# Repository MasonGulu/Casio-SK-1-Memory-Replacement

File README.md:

# Casio-SK-1-Memory-Replacement
A memory replacement PCB that adds sample loading and saving to the SK-1

This has not been tested yet and is still in early stages of development

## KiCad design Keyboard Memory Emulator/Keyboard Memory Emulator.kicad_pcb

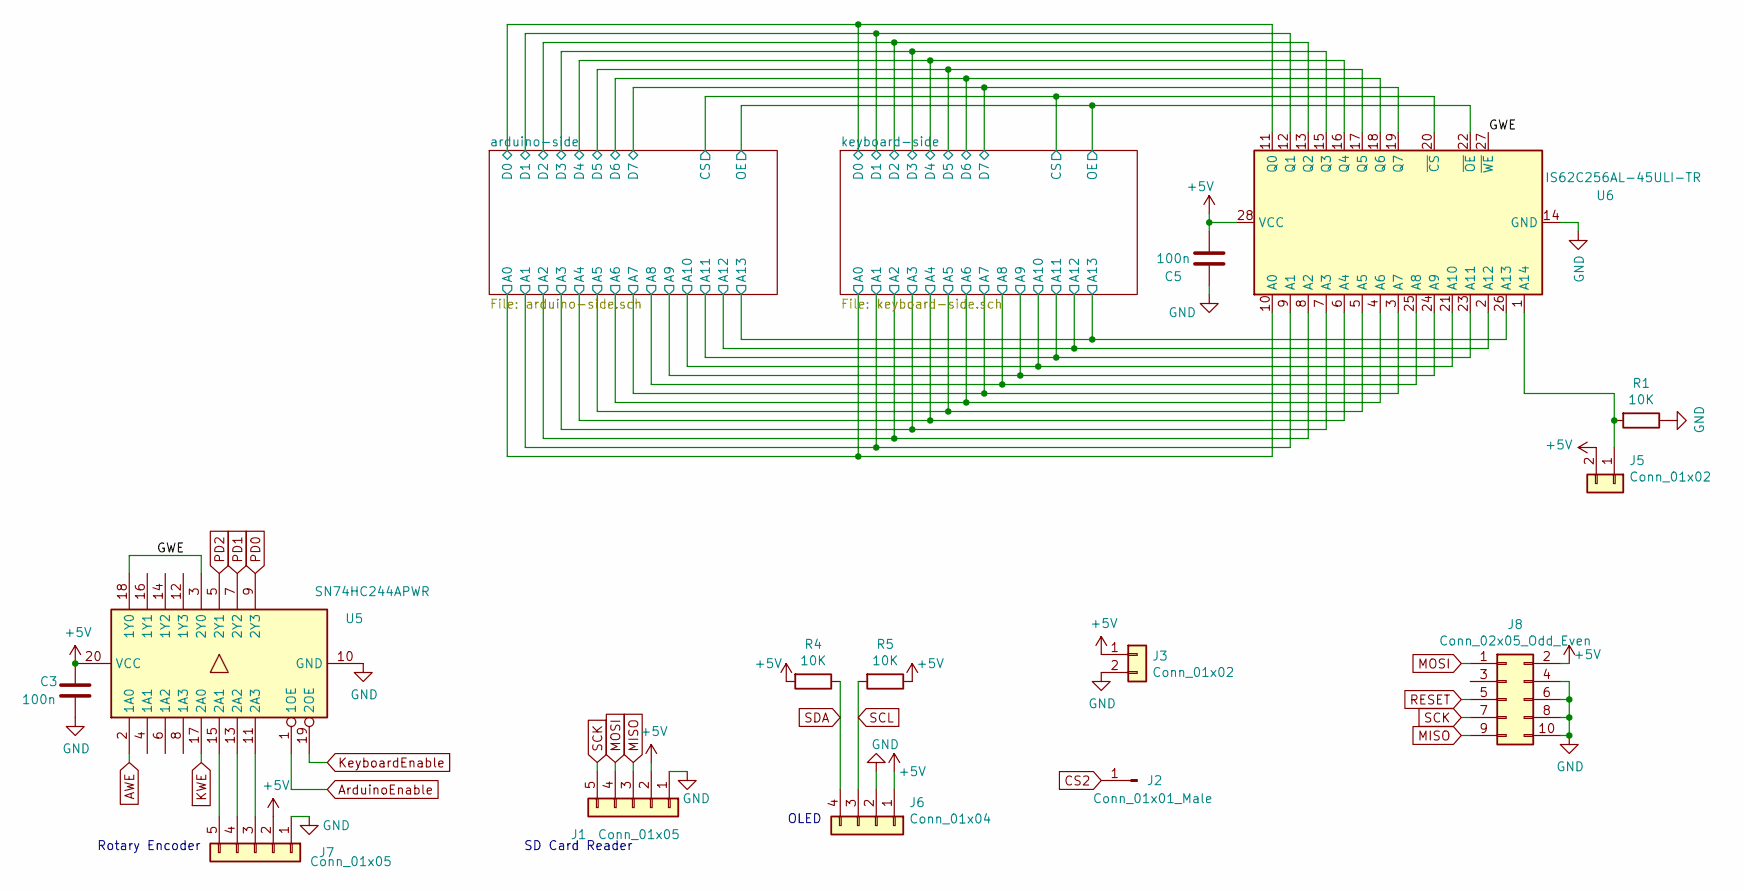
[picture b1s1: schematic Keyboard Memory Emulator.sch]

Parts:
C3, C5: 100n; C_Disc_D5.1mm_W3.2mm_P5.00mm
J1, J7: Conn_01x05; PinHeader_1x05_P2.54mm_Vertical
J2: Conn_01x01_Male; PinHeader_1x01_P2.54mm_Vertical
J3, J5: Conn_01x02; PinHeader_1x02_P2.54mm_Vertical
J6: Conn_01x04; PinHeader_1x04_P2.54mm_Vertical
J8: Conn_02x05_Odd_Even; PinHeader_2x05_P2.54mm_Vertical
R1, R4, R5: 10K; R_Axial_DIN0204_L3.6mm_D1.6mm_P5.08mm_Horizontal
U5: SN74HC244APWR; TSSOP-20_4.4x6.5mm_P0.65mm
U6: IS62C256AL-45ULI-TR; SOIC-28W_7.5x18.7mm_P1.27mm

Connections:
+5V: C3.1, C5.2, J1.2, J3.1, J5.2, J6.1, J7.2, J8.2, R4.2, R5.1, U5.20 (VCC), U6.28 (VCC); also elsewhere on the board
/GWE: U5.3 (2Y0), U5.18 (1Y0), U6.27 (~WE)
/PD0: U5.9 (2Y3)
/PD1: U5.7 (2Y2)
/PD2: U5.5 (2Y1)
/arduino-side/A0: U6.10 (A0); also elsewhere on the board
/arduino-side/A1: U6.9 (A1); also elsewhere on the board
/arduino-side/A2: U6.8 (A2); also elsewhere on the board
/arduino-side/A3: U6.7 (A3); also elsewhere on the board
/arduino-side/A4: U6.6 (A4); also elsewhere on the board
/arduino-side/A5: U6.5 (A5); also elsewhere on the board
/arduino-side/A6: U6.4 (A6); also elsewhere on the board
/arduino-side/A7: U6.3 (A7); also elsewhere on the board
/arduino-side/A8: U6.25 (A8); also elsewhere on the board
/arduino-side/A9: U6.24 (A9); also elsewhere on the board
/arduino-side/A10: U6.21 (A10); also elsewhere on the board
/arduino-side/A11: U6.23 (A11); also elsewhere on the board
/arduino-side/A12: U6.2 (A12); also elsewhere on the board
/arduino-side/A13: U6.26 (A13); also elsewhere on the board
/arduino-side/CS: U6.20 (~CS); also elsewhere on the board
/arduino-side/D0: U6.11 (Q0); also elsewhere on the board
/arduino-side/D1: U6.12 (Q1); also elsewhere on the board
/arduino-side/D2: U6.13 (Q2); also elsewhere on the board
/arduino-side/D3: U6.15 (Q3); also elsewhere on the board
/arduino-side/D4: U6.16 (Q4); also elsewhere on the board
/arduino-side/D5: U6.17 (Q5); also elsewhere on the board
/arduino-side/D6: U6.18 (Q6); also elsewhere on the board
/arduino-side/D7: U6.19 (Q7); also elsewhere on the board
AWE: U5.2 (1A0); also elsewhere on the board
ArduinoEnable: U5.1 (1OE); also elsewhere on the board
CS2: J2.1; also elsewhere on the board
GND: C3.2, C5.1, J1.1, J3.2, J6.2, J7.1, J8.4, J8.6, J8.8, J8.10, R1.1, U5.10 (GND), U6.14 (GND); also elsewhere on the board
KWE: U5.17 (2A0); also elsewhere on the board
KeyboardEnable: U5.19 (2OE); also elsewhere on the board
MISO: J1.3, J8.9; also elsewhere on the board
MOSI: J1.4, J8.1; also elsewhere on the board
unnamed: J5.1, R1.2, U6.1 (A14)
unnamed: J7.3, U5.11 (2A3)
unnamed: J7.4, U5.13 (2A2)
unnamed: J7.5, U5.15 (2A1)
OE: U6.22 (~OE); also elsewhere on the board
RESET: J8.5; also elsewhere on the board
SCK: J1.5, J8.7; also elsewhere on the board
SCL: J6.3, R5.2; also elsewhere on the board
SDA: J6.4, R4.1; also elsewhere on the board

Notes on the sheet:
SD Card Reader
OLED
Rotary Encoder

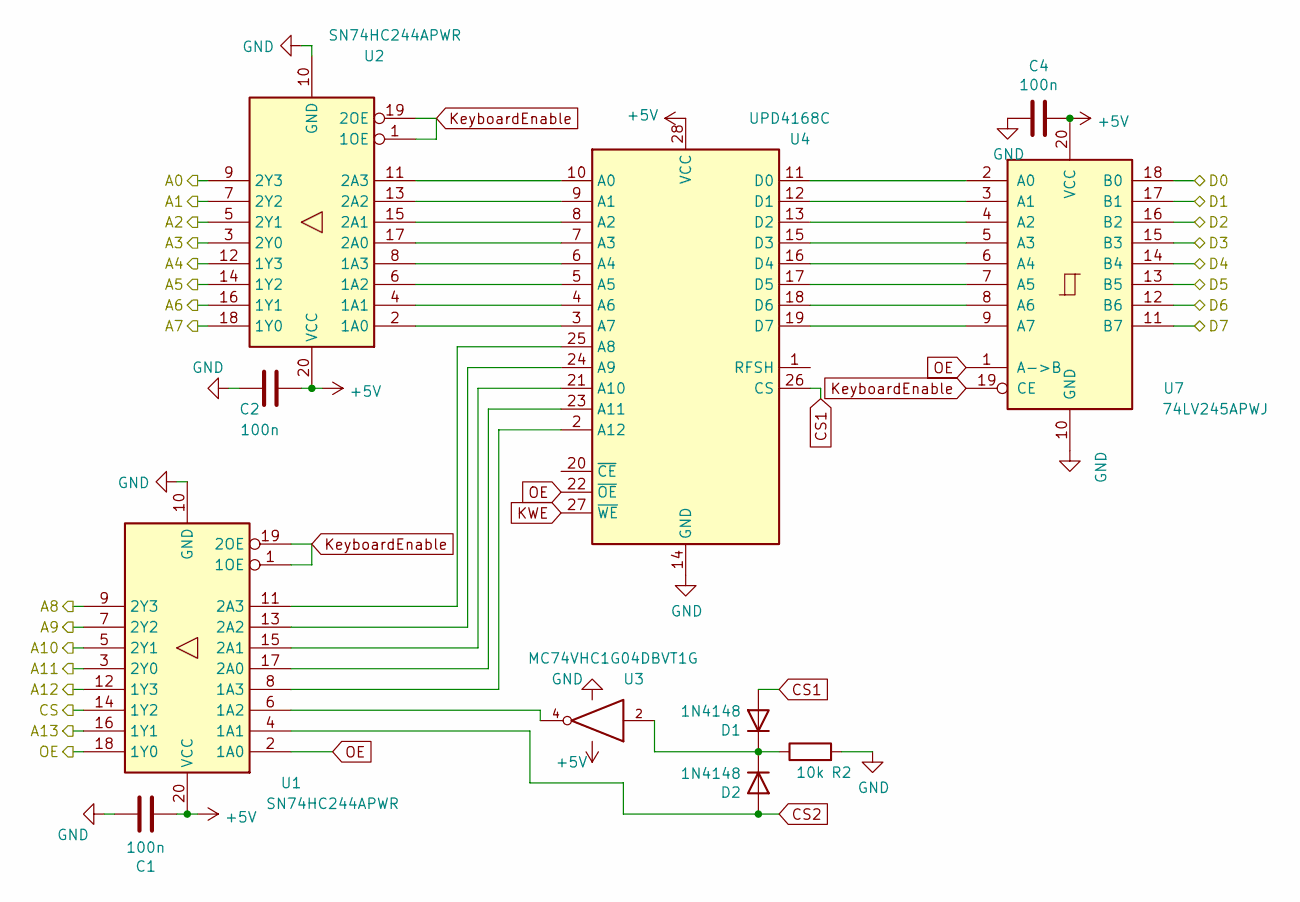
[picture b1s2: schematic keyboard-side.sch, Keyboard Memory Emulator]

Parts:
C1, C2, C4: 100n; C_Disc_D5.1mm_W3.2mm_P5.00mm
D1, D2: 1N4148; D_DO-34_SOD68_P7.62mm_Horizontal
R2: 10k; R_Axial_DIN0204_L3.6mm_D1.6mm_P5.08mm_Horizontal
U1, U2: SN74HC244APWR; TSSOP-20_4.4x6.5mm_P0.65mm
U3: MC74VHC1G04DBVT1G; SC-74A
U4: UPD4168C; DIP-28_W15.24mm
U7: 74LV245APWJ; TSSOP-20_4.4x6.5mm_P0.65mm

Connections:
+5V: C1.2, C2.1, C4.1, U1.20 (VCC), U2.20 (VCC), U3.5 (VCC), U4.28 (VCC), U7.20 (VCC); also elsewhere on the board
/arduino-side/A0: U2.9 (2Y3); also elsewhere on the board
/arduino-side/A1: U2.7 (2Y2); also elsewhere on the board
/arduino-side/A2: U2.5 (2Y1); also elsewhere on the board
/arduino-side/A3: U2.3 (2Y0); also elsewhere on the board
/arduino-side/A4: U2.12 (1Y3); also elsewhere on the board
/arduino-side/A5: U2.14 (1Y2); also elsewhere on the board
/arduino-side/A6: U2.16 (1Y1); also elsewhere on the board
/arduino-side/A7: U2.18 (1Y0); also elsewhere on the board
/arduino-side/A8: U1.9 (2Y3); also elsewhere on the board
/arduino-side/A9: U1.7 (2Y2); also elsewhere on the board
/arduino-side/A10: U1.5 (2Y1); also elsewhere on the board
/arduino-side/A11: U1.3 (2Y0); also elsewhere on the board
/arduino-side/A12: U1.12 (1Y3); also elsewhere on the board
/arduino-side/A13: U1.16 (1Y1); also elsewhere on the board
/arduino-side/CS: U1.14 (1Y2); also elsewhere on the board
/arduino-side/D0: U7.18 (B0); also elsewhere on the board
/arduino-side/D1: U7.17 (B1); also elsewhere on the board
/arduino-side/D2: U7.16 (B2); also elsewhere on the board
/arduino-side/D3: U7.15 (B3); also elsewhere on the board
/arduino-side/D4: U7.14 (B4); also elsewhere on the board
/arduino-side/D5: U7.13 (B5); also elsewhere on the board
/arduino-side/D6: U7.12 (B6); also elsewhere on the board
/arduino-side/D7: U7.11 (B7); also elsewhere on the board
CS1: D1.2 (A), U4.26 (CS)
CS2: D2.2 (A), U1.4 (1A1); also elsewhere on the board
GND: C1.1, C2.2, C4.2, R2.2, U1.10 (GND), U2.10 (GND), U3.3 (GND), U4.14 (GND), U7.10 (GND); also elsewhere on the board
KWE: U4.27 (~WE~); also elsewhere on the board
KeyboardEnable: U1.1 (1OE), U1.19 (2OE), U2.1 (1OE), U2.19 (2OE), U7.19 (CE); also elsewhere on the board
unnamed: D1.1 (K), D2.1 (K), R2.1, U3.2
unnamed: U1.6 (1A2), U3.4
unnamed: U1.8 (1A3), U4.2 (A12)
unnamed: U1.11 (2A3), U4.25 (A8)
unnamed: U1.13 (2A2), U4.24 (A9)
unnamed: U1.15 (2A1), U4.21 (A10)
unnamed: U1.17 (2A0), U4.23 (A11)
unnamed: U2.2 (1A0), U4.3 (A7)
unnamed: U2.4 (1A1), U4.4 (A6)
unnamed: U2.6 (1A2), U4.5 (A5)
unnamed: U2.8 (1A3), U4.6 (A4)
unnamed: U2.11 (2A3), U4.10 (A0)
unnamed: U2.13 (2A2), U4.9 (A1)
unnamed: U2.15 (2A1), U4.8 (A2)
unnamed: U2.17 (2A0), U4.7 (A3)
unnamed: U4.11 (D0), U7.2 (A0)
unnamed: U4.12 (D1), U7.3 (A1)
unnamed: U4.13 (D2), U7.4 (A2)
unnamed: U4.15 (D3), U7.5 (A3)
unnamed: U4.16 (D4), U7.6 (A4)
unnamed: U4.17 (D5), U7.7 (A5)
unnamed: U4.18 (D6), U7.8 (A6)
unnamed: U4.19 (D7), U7.9 (A7)
OE: U1.2 (1A0), U1.18 (1Y0), U4.22 (~OE~), U7.1 (A->B); also elsewhere on the board

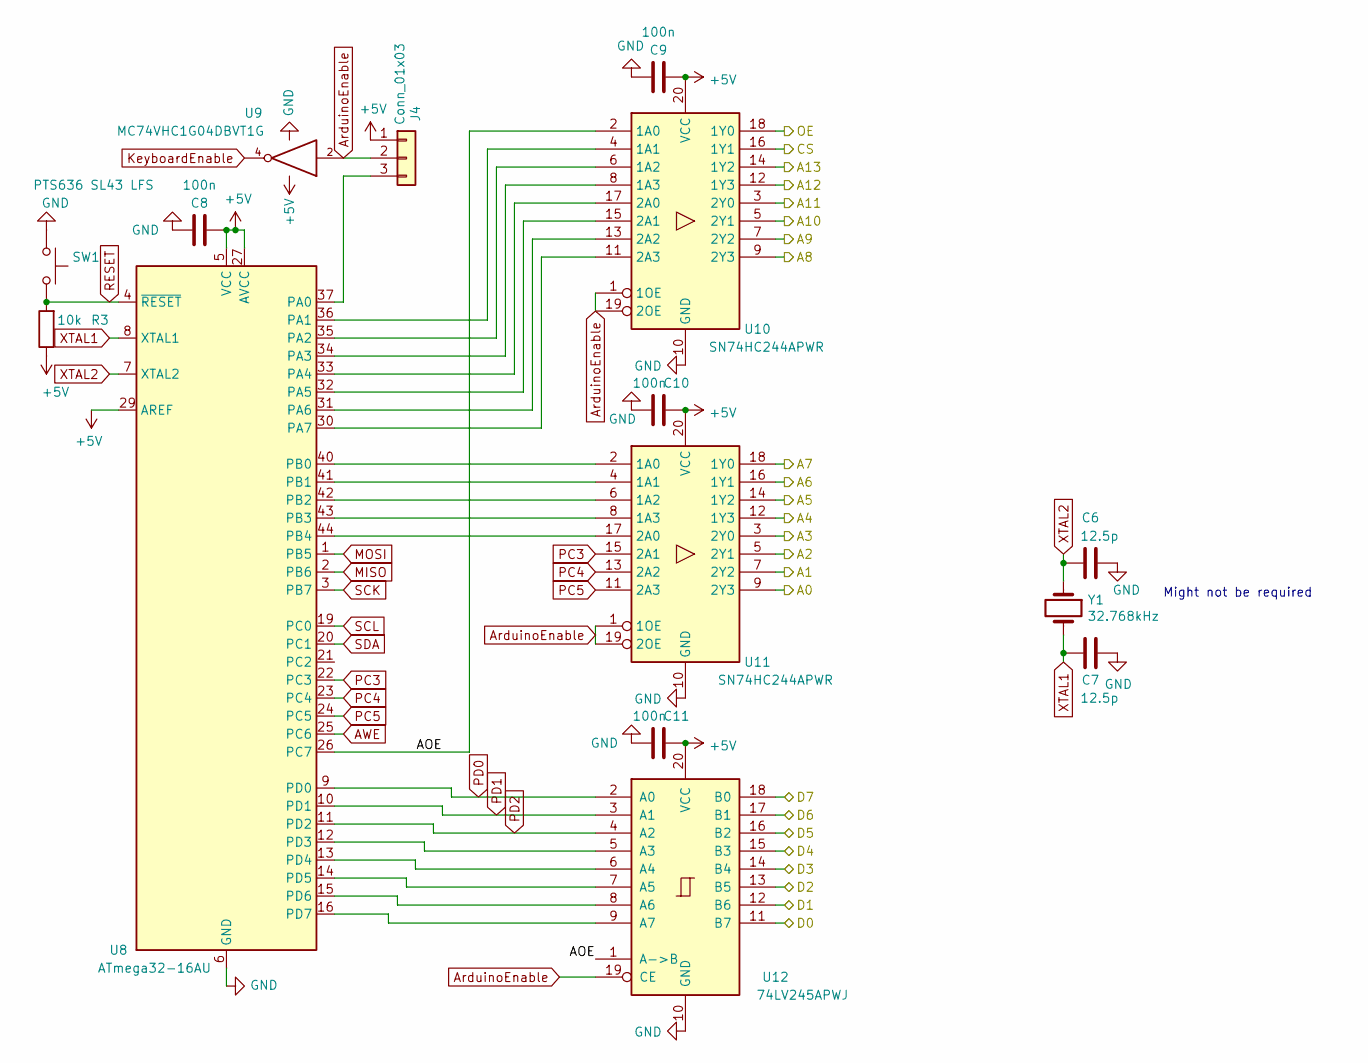
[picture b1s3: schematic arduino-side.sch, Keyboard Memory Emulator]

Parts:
C6, C7: 12.5p; C_Disc_D5.1mm_W3.2mm_P5.00mm
C8, C9, C10, C11: 100n; C_Disc_D5.1mm_W3.2mm_P5.00mm
J4: Conn_01x03; PinHeader_1x03_P2.54mm_Vertical
R3: 10k; R_Axial_DIN0204_L3.6mm_D1.6mm_P5.08mm_Horizontal
SW1: PTS636 SL43 LFS; SW_SPST_REED_CT05-XXXX-G1
U8: ATmega32-16AU; TQFP-44_10x10mm_P0.8mm
U9: MC74VHC1G04DBVT1G; SC-74A
U10, U11: SN74HC244APWR; TSSOP-20_4.4x6.5mm_P0.65mm
U12: 74LV245APWJ; TSSOP-20_4.4x6.5mm_P0.65mm
Y1: 32.768kHz; Crystal_C26-LF_D2.1mm_L6.5mm_Horizontal

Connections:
+5V: C8.2, C9.2, C10.2, C11.2, J4.1, R3.1, U8.5 (VCC), U8.17 (VCC), U8.27 (AVCC), U8.29 (AREF), U8.38 (VCC), U9.5 (VCC), U10.20 (VCC), U11.20 (VCC), U12.20 (VCC); also elsewhere on the board
/arduino-side/A0: U11.9 (2Y3); also elsewhere on the board
/arduino-side/A1: U11.7 (2Y2); also elsewhere on the board
/arduino-side/A2: U11.5 (2Y1); also elsewhere on the board
/arduino-side/A3: U11.3 (2Y0); also elsewhere on the board
/arduino-side/A4: U11.12 (1Y3); also elsewhere on the board
/arduino-side/A5: U11.14 (1Y2); also elsewhere on the board
/arduino-side/A6: U11.16 (1Y1); also elsewhere on the board
/arduino-side/A7: U11.18 (1Y0); also elsewhere on the board
/arduino-side/A8: U10.9 (2Y3); also elsewhere on the board
/arduino-side/A9: U10.7 (2Y2); also elsewhere on the board
/arduino-side/A10: U10.5 (2Y1); also elsewhere on the board
/arduino-side/A11: U10.3 (2Y0); also elsewhere on the board
/arduino-side/A12: U10.12 (1Y3); also elsewhere on the board
/arduino-side/A13: U10.14 (1Y2); also elsewhere on the board
/arduino-side/AOE: U8.26 (PC7), U10.2 (1A0), U12.1 (A->B)
/arduino-side/CS: U10.16 (1Y1); also elsewhere on the board
/arduino-side/D0: U12.11 (B7); also elsewhere on the board
/arduino-side/D1: U12.12 (B6); also elsewhere on the board
/arduino-side/D2: U12.13 (B5); also elsewhere on the board
/arduino-side/D3: U12.14 (B4); also elsewhere on the board
/arduino-side/D4: U12.15 (B3); also elsewhere on the board
/arduino-side/D5: U12.16 (B2); also elsewhere on the board
/arduino-side/D6: U12.17 (B1); also elsewhere on the board
/arduino-side/D7: U12.18 (B0); also elsewhere on the board
/arduino-side/PD0: U8.9 (PD0), U12.2 (A0)
/arduino-side/PD1: U8.10 (PD1), U12.3 (A1)
/arduino-side/PD2: U8.11 (PD2), U12.4 (A2)
AWE: U8.25 (PC6); also elsewhere on the board
ArduinoEnable: J4.2, U9.2, U10.1 (1OE), U10.19 (2OE), U11.1 (1OE), U11.19 (2OE), U12.19 (CE); also elsewhere on the board
GND: C6.1, C7.1, C8.1, C9.1, C10.1, C11.1, SW1.1, U8.6 (GND), U8.18 (GND), U8.28 (GND), U8.39 (GND), U9.3 (GND), U10.10 (GND), U11.10 (GND), U12.10 (GND); also elsewhere on the board
KeyboardEnable: U9.4; also elsewhere on the board
MISO: U8.2 (PB6); also elsewhere on the board
MOSI: U8.1 (PB5); also elsewhere on the board
unnamed: J4.3, U8.37 (PA0)
unnamed: U8.36 (PA1), U10.4 (1A1)
unnamed: U8.35 (PA2), U10.6 (1A2)
unnamed: U8.34 (PA3), U10.8 (1A3)
unnamed: U8.30 (PA7), U10.11 (2A3)
unnamed: U8.31 (PA6), U10.13 (2A2)
unnamed: U8.32 (PA5), U10.15 (2A1)
unnamed: U8.33 (PA4), U10.17 (2A0)
unnamed: U8.40 (PB0), U11.2 (1A0)
unnamed: U8.41 (PB1), U11.4 (1A1)
unnamed: U8.42 (PB2), U11.6 (1A2)
unnamed: U8.43 (PB3), U11.8 (1A3)
unnamed: U8.44 (PB4), U11.17 (2A0)
unnamed: U8.12 (PD3), U12.5 (A3)
unnamed: U8.13 (PD4), U12.6 (A4)
unnamed: U8.14 (PD5), U12.7 (A5)
unnamed: U8.15 (PD6), U12.8 (A6)
unnamed: U8.16 (PD7), U12.9 (A7)
OE: U10.18 (1Y0); also elsewhere on the board
PC3: U8.22 (PC3), U11.15 (2A1)
PC4: U8.23 (PC4), U11.13 (2A2)
PC5: U8.24 (PC5), U11.11 (2A3)
RESET: R3.2, SW1.2, U8.4 (~RESET); also elsewhere on the board
SCK: U8.3 (PB7); also elsewhere on the board
SCL: U8.19 (PC0); also elsewhere on the board
SDA: U8.20 (PC1); also elsewhere on the board
XTAL1: C7.2, U8.8 (XTAL1), Y1.2
XTAL2: C6.2, U8.7 (XTAL2), Y1.1

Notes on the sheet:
Might not be required

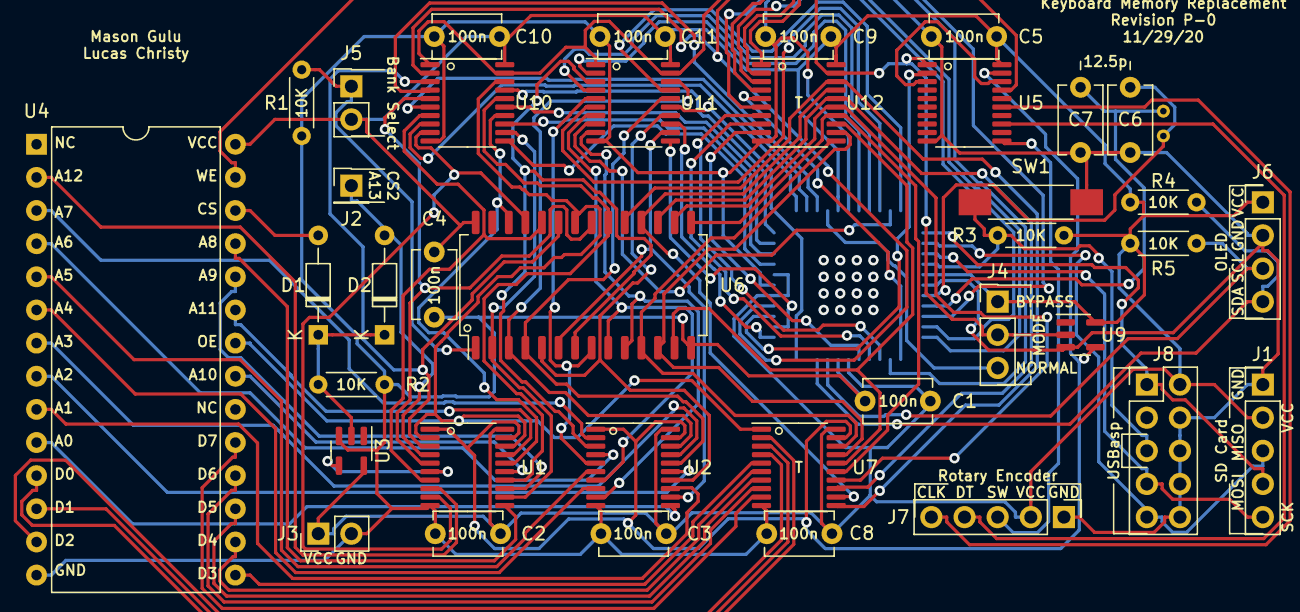
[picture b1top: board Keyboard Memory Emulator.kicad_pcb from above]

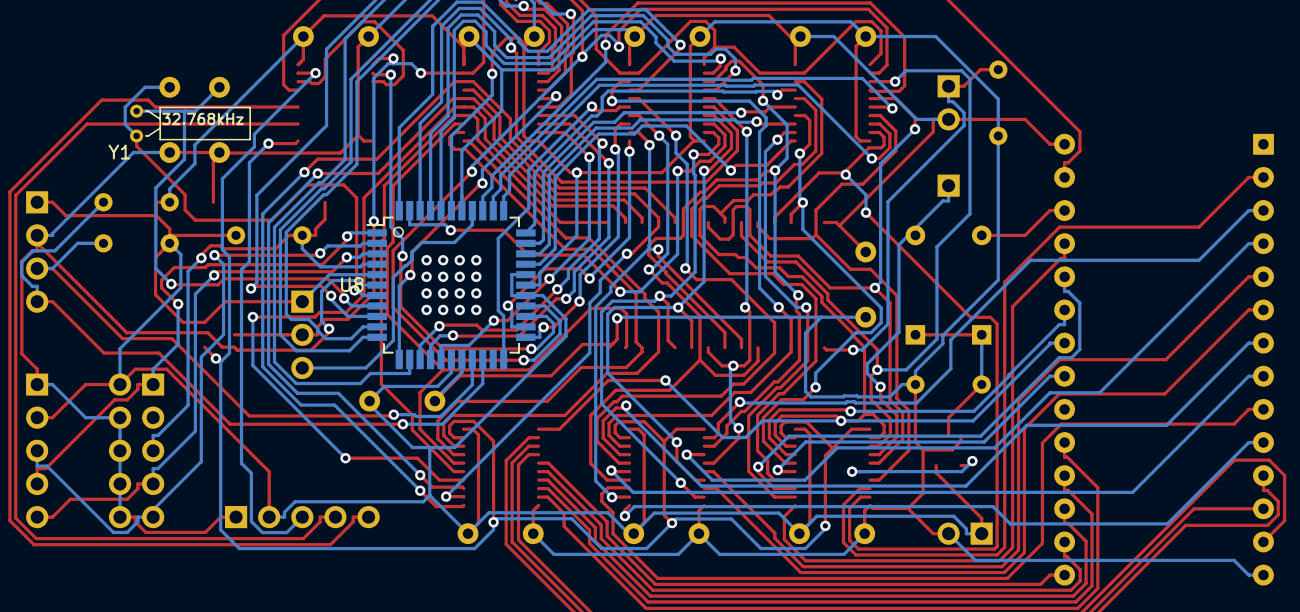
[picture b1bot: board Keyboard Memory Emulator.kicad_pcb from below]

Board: 2 copper layers, 40 parts (2 on the bottom side), 93 nets.

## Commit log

2020-11-02 Getting closer to finalization
    With this update I believe it should be ready to order, waiting to get it looked over beforehand
2020-11-29 Schematic Restructuring to make it cleaner and easier to read. No actual changes as of yet, but planning to add some pull-up resistors on the I2C data bus.
2020-11-29 Part 2 of the previous commit, as though the new schematics weren't included
2020-11-30 Ran the autorouter and updated the PCB
2020-11-30 Added pin 1 indicators on silkscreen for SMD components
2020-11-30 Updated PCB sheet information
2020-11-30 Added labels on PCB, and adjusted font sizes to match jlcpcb's requirements.
2020-12-24 Added a gitignore, hopefully it will work as I hope. I also fixed the traces that were not showing up due to improper nets.
